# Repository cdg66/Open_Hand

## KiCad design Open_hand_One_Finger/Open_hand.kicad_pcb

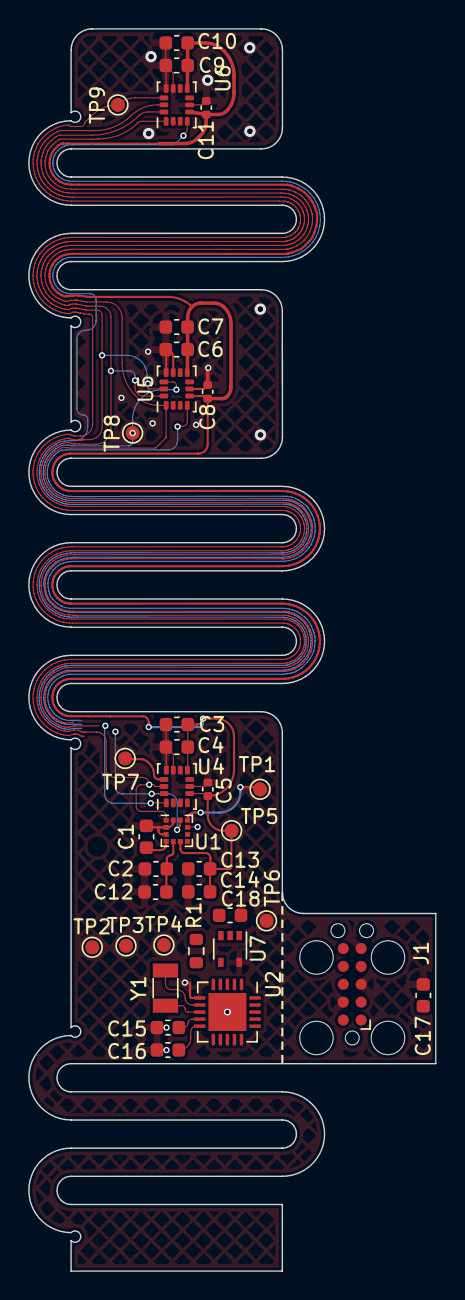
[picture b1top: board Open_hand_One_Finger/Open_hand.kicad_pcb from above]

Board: 2 copper layers, 28.9 x 88.2 mm, 37 parts (1 on the bottom side), 26 nets.

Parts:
C1, C2, C4, C7, C10, C14: 100n; C_0603_1608Metric
C3, C6, C9: 2u2; C_0603_1608Metric
C5, C8, C11: 10n; C_0402_1005Metric
C12, C13, C15, C16, C17, C18: 1u; C_0603_1608Metric
J1: Conn_ARM_JTAG_SWD_10; Tag-Connect_TC2050-IDC-FP_2x05_P1.27mm_Vertical
J2: DF37C-24DP-0.4V(51)
R1: R_US; R_0603_1608Metric
TP1, TP2, TP3, TP4, TP5, TP6, TP7, TP8, TP9: TestPoint; TestPoint_Pad_D1.0mm
U1: LIS3MDL; LGA-12_2x2mm_P0.5mm
U2: MAX32660GTP; TQFN-20-1EP_4x4mm_P0.5mm_EP2.7x2.7mm
U4, U5, U6: ICM-40608; LGA-14_3x2.5mm_P0.5mm_LayoutBorder3x4y
U7: SN74AHC1G02DCKR; SOT-353_SC-70-5
Y1: 32.768kHz,6pF; Crystal_SMD_3215-2Pin_3.2x1.5mm

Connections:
+3.3V: C2.1, C3.1, C4.1, C5.1, C6.1, C7.1, C8.1, C9.1, C10.1, C11.1, C12.1, C13.1, C14.1, C15.1, C17.1, C18.1, J1.1 (VTref), J2.6, J2.8, R1.1, TP5.1, U1.5 (Vdd), U1.6 (Vdd_IO), U2.9 (VDD), U4.5 (VDDIO), U4.8 (VDD), U5.5 (VDDIO), U5.8 (VDD), U6.5 (VDDIO), U6.8 (VDD), U7.3 (GND)
/CLK: J2.17, TP2.1, U1.1 (SCL/SPC), U2.16 (P0.6), U4.13 (AP_SCLK/AP_SCL), U5.13 (AP_SCLK/AP_SCL), U6.13 (AP_SCLK/AP_SCL)
/CS0: J2.15, TP7.1, U2.15 (P0.7), U4.12 (AP_CS)
/CS1: J2.13, TP8.1, U2.14 (P0.10), U5.12 (AP_CS)
/CS2: J2.11, TP9.1, U2.13 (P0.11), U6.12 (AP_CS)
/CS_MAG: J2.9, TP1.1, U1.10 (~CS), U2.4 (P0.12)
/DIN: J2.19, TP3.1, U1.11 (SDA/SDI/SDO), U2.17 (P0.5), U4.14 (AP_SDI/AP_SDIO/AP_SDA), U5.14 (AP_SDI/AP_SDIO/AP_SDA), U6.14 (AP_SDI/AP_SDIO/AP_SDA)
/DOUT: J2.21, TP4.1, U1.9 (SDO/SA1), U2.18 (P0.4), U4.1 (AP_SDO/AP_AD0), U5.1 (AP_SDO/AP_AD0), U6.1 (AP_SDO/AP_AD0)
/DREADY: J2.4, U1.8 (DRDY), U7.2
/INT0: J2.5, U4.4 (INT1/INT)
/INT1: J2.3, U5.4 (INT1/INT)
/INT2: J2.2, U6.4 (INT1/INT), U7.1
/INT_MAG: J2.1, U1.7 (INT)
/RST: J1.10 (~RESET), R1.2, U2.5 (~RSTN)
/SWCLK: J1.4 (SWDCLK/TCK), J2.14, U2.11 (P0.9)
/SWIO: J1.2 (SWDIO/TMS), J2.12, U2.12 (P0.8)
/UFP_CLK: J2.20, U2.20 (P0.2)
/UFP_CS: J2.22, U2.19 (P0.3)
/UFP_MISO: J2.16, U2.2 (P0.0)
/UFP_MOSI: J2.18, U2.1 (P0.1)
GND: C1.2, C2.2, C3.2, C4.2, C5.2, C6.2, C7.2, C8.2, C9.2, C10.2, C11.2, C12.2, C13.2, C14.2, C15.2, C16.2, C17.2, C18.2, J1.3 (GND), J1.5 (GND), J1.9 (GNDDetect), J2.7, J2.10, J2.23, J2.24, TP6.1, U1.2 (GND), U1.3 (GND), U1.12 (GND), U2.6 (V_{SS}), U2.21 (V_{SS}), U4.6 (GND), U4.10 (RESV), U4.11 (RESV), U5.6 (GND), U5.10 (RESV), U5.11 (RESV), U6.6 (GND), U6.10 (RESV), U6.11 (RESV), U7.5 (VCC)
unnamed: C1.1, U1.4 (C1)
unnamed: U2.8 (32KIN), Y1.1
unnamed: U2.7 (32KOUT), Y1.2
unnamed: U2.3 (P0.13), U7.4
unnamed: C16.1, U2.10 (VCORE)

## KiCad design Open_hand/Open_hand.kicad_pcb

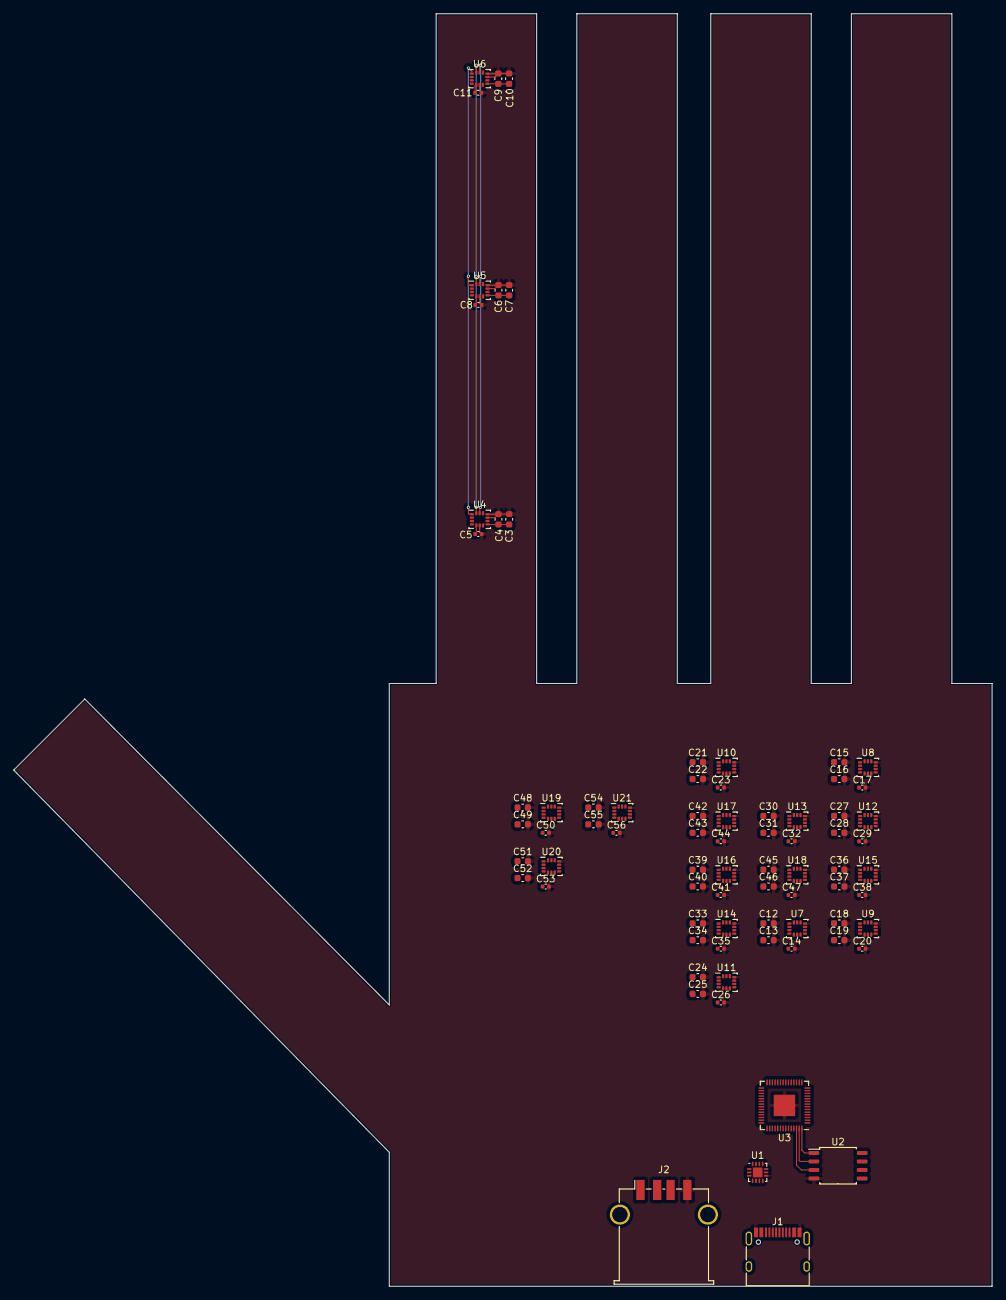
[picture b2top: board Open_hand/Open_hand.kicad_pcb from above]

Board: 2 copper layers, 146.1 x 190.0 mm, 77 parts (0 on the bottom side), 20 nets.

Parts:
C3, C6, C9, C12, C15, C18, C21, C24, C27, C30, C33, C36, C39, C42, C45, C48, C51, C54: 2u2; C_0603_1608Metric
C4, C7, C10, C13, C16, C19, C22, C25, C28, C31, C34, C37, C40, C43, C46, C49, C52, C55: 100n; C_0603_1608Metric
C5, C8, C11, C14, C17, C20, C23, C26, C29, C32, C35, C38, C41, C44, C47, C50, C53, C56: 10n; C_0402_1005Metric
J1: USB_C_Receptacle_USB2.0; USB_C_Receptacle_HRO_TYPE-C-31-M-12
J2: USB_A; USB_A_TE_292303-7_Horizontal
U1: FUSB302B10MPX; WQFN-14-1EP_2.5x2.5mm_P0.5mm_EP1.45x1.45mm
U2: W25Q16JVSS; SOIC-8_5.23x5.23mm_P1.27mm
U3: RP2040; QFN-56-1EP_7x7mm_P0.4mm_EP3.2x3.2mm
U4, U5, U6, U7, U8, U9, U10, U11, U12, U13, U14, U15, U16, U17, U18, U19, U20, U21: ICM-40608; LGA-14_3x2.5mm_P0.5mm_LayoutBorder3x4y

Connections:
+3.3V: C3.1, C4.1, C5.1, C6.1, C7.1, C8.1, C9.1, C10.1, C11.1, C12.1, C13.1, C14.1, C15.1, C16.1, C17.1, C18.1, C19.1, C20.1, C21.1, C22.1, C23.1, C24.1, C25.1, C26.1, C27.1, C28.1, C29.1, C30.1, C31.1, C32.1, C33.1, C34.1, C35.1, C36.1, C37.1, C38.1, C39.1, C40.1, C41.1, C42.1, C43.1, C44.1, C45.1, C46.1, C47.1, C48.1, C49.1, C50.1, C51.1, C52.1, C53.1, C54.1, C55.1, C56.1, U1.3 (VDD), U1.4 (VDD), U4.5 (VDDIO), U4.8 (VDD), U5.5 (VDDIO), U5.8 (VDD), U6.5 (VDDIO), U6.8 (VDD), U7.5 (VDDIO), U7.8 (VDD), U8.5 (VDDIO), U8.8 (VDD), U9.5 (VDDIO), U9.8 (VDD), U10.5 (VDDIO), U10.8 (VDD), U11.5 (VDDIO), U11.8 (VDD), U12.5 (VDDIO), U12.8 (VDD), U13.5 (VDDIO), U13.8 (VDD), U14.5 (VDDIO), U14.8 (VDD), U15.5 (VDDIO), U15.8 (VDD), U16.5 (VDDIO), U16.8 (VDD), U17.5 (VDDIO), U17.8 (VDD), U18.5 (VDDIO), U18.8 (VDD), U19.5 (VDDIO), U19.8 (VDD), U20.5 (VDDIO), U20.8 (VDD), U21.5 (VDDIO), U21.8 (VDD)
/CLK: U4.13 (AP_SCLK/AP_SCL), U5.13 (AP_SCLK/AP_SCL), U6.13 (AP_SCLK/AP_SCL), U7.13 (AP_SCLK/AP_SCL), U8.13 (AP_SCLK/AP_SCL), U9.13 (AP_SCLK/AP_SCL), U10.13 (AP_SCLK/AP_SCL), U11.13 (AP_SCLK/AP_SCL), U12.13 (AP_SCLK/AP_SCL), U13.13 (AP_SCLK/AP_SCL), U14.13 (AP_SCLK/AP_SCL), U15.13 (AP_SCLK/AP_SCL), U16.13 (AP_SCLK/AP_SCL), U17.13 (AP_SCLK/AP_SCL), U18.13 (AP_SCLK/AP_SCL), U19.13 (AP_SCLK/AP_SCL), U20.13 (AP_SCLK/AP_SCL), U21.13 (AP_SCLK/AP_SCL)
/CPU/D_M: J1.A7 (D-), J1.B7 (D-), U3.46 (USB_DM)
/CPU/D_P: J1.A6 (D+), J1.B6 (D+), U3.47 (USB_DP)
/DIN: U4.14 (AP_SDI/AP_SDIO/AP_SDA), U5.14 (AP_SDI/AP_SDIO/AP_SDA), U6.14 (AP_SDI/AP_SDIO/AP_SDA), U7.14 (AP_SDI/AP_SDIO/AP_SDA), U8.14 (AP_SDI/AP_SDIO/AP_SDA), U9.14 (AP_SDI/AP_SDIO/AP_SDA), U10.14 (AP_SDI/AP_SDIO/AP_SDA), U11.14 (AP_SDI/AP_SDIO/AP_SDA), U12.14 (AP_SDI/AP_SDIO/AP_SDA), U13.14 (AP_SDI/AP_SDIO/AP_SDA), U14.14 (AP_SDI/AP_SDIO/AP_SDA), U15.14 (AP_SDI/AP_SDIO/AP_SDA), U16.14 (AP_SDI/AP_SDIO/AP_SDA), U17.14 (AP_SDI/AP_SDIO/AP_SDA), U18.14 (AP_SDI/AP_SDIO/AP_SDA), U19.14 (AP_SDI/AP_SDIO/AP_SDA), U20.14 (AP_SDI/AP_SDIO/AP_SDA), U21.14 (AP_SDI/AP_SDIO/AP_SDA)
/DOUT: U4.1 (AP_SDO/AP_AD0), U5.1 (AP_SDO/AP_AD0), U6.1 (AP_SDO/AP_AD0), U7.1 (AP_SDO/AP_AD0), U8.1 (AP_SDO/AP_AD0), U9.1 (AP_SDO/AP_AD0), U10.1 (AP_SDO/AP_AD0), U11.1 (AP_SDO/AP_AD0), U12.1 (AP_SDO/AP_AD0), U13.1 (AP_SDO/AP_AD0), U14.1 (AP_SDO/AP_AD0), U15.1 (AP_SDO/AP_AD0), U16.1 (AP_SDO/AP_AD0), U17.1 (AP_SDO/AP_AD0), U18.1 (AP_SDO/AP_AD0), U19.1 (AP_SDO/AP_AD0), U20.1 (AP_SDO/AP_AD0), U21.1 (AP_SDO/AP_AD0)
GND: C3.2, C4.2, C5.2, C6.2, C7.2, C8.2, C9.2, C10.2, C11.2, C12.2, C13.2, C14.2, C15.2, C16.2, C17.2, C18.2, C19.2, C20.2, C21.2, C22.2, C23.2, C24.2, C25.2, C26.2, C27.2, C28.2, C29.2, C30.2, C31.2, C32.2, C33.2, C34.2, C35.2, C36.2, C37.2, C38.2, C39.2, C40.2, C41.2, C42.2, C43.2, C44.2, C45.2, C46.2, C47.2, C48.2, C49.2, C50.2, C51.2, C52.2, C53.2, C54.2, C55.2, C56.2, J1.A1 (GND), J1.A12 (GND), J1.B1 (GND), J1.B12 (GND), J2.4 (GND), U1.8 (GND), U1.9 (GND), U1.15 (GND), U2.4 (GND), U3.57 (GND), U4.6 (GND), U4.10 (RESV), U4.11 (RESV), U5.6 (GND), U5.10 (RESV), U5.11 (RESV), U6.6 (GND), U6.10 (RESV), U6.11 (RESV), U7.6 (GND), U7.10 (RESV), U7.11 (RESV), U8.6 (GND), U8.10 (RESV), U8.11 (RESV), U9.6 (GND), U9.10 (RESV), U9.11 (RESV), U10.6 (GND), U10.10 (RESV), U10.11 (RESV), U11.6 (GND), U11.10 (RESV), U11.11 (RESV), U12.6 (GND), U12.10 (RESV), U12.11 (RESV), U13.6 (GND), U13.10 (RESV), U13.11 (RESV), U14.6 (GND), U14.10 (RESV), U14.11 (RESV), U15.6 (GND), U15.10 (RESV), U15.11 (RESV), U16.6 (GND), U16.10 (RESV), U16.11 (RESV), U17.6 (GND), U17.10 (RESV), U17.11 (RESV), U18.6 (GND), U18.10 (RESV), U18.11 (RESV), U19.6 (GND), U19.10 (RESV), U19.11 (RESV), U20.6 (GND), U20.10 (RESV), U20.11 (RESV), U21.6 (GND), U21.10 (RESV), U21.11 (RESV)
unnamed: J1.A5 (CC1), U1.10 (CC1), U1.11 (CC1)
unnamed: J1.B5 (CC2), U1.1 (CC2), U1.14 (CC2)
unnamed: J2.3 (D+), U3.27 (GPIO16)
unnamed: J2.2 (D-), U3.28 (GPIO17)
unnamed: U2.6 (CLK), U3.52 (QSPI_SCLK)
unnamed: U2.5 (DI(IO0)), U3.53 (QSPI_SD0)
unnamed: U2.2 (DO(IO1)), U3.55 (QSPI_SD1)
unnamed: U2.3 (IO2), U3.54 (QSPI_SD2)
unnamed: U2.7 (IO3), U3.51 (QSPI_SD3)
unnamed: U2.1 (~CS), U3.56 (QSPI_SS)
unnamed: U3.23 (DVDD), U3.50 (DVDD)
unnamed: U3.1 (IOVDD), U3.10 (IOVDD), U3.22 (IOVDD), U3.33 (IOVDD), U3.42 (IOVDD), U3.49 (IOVDD)
VBUS: J1.A4 (VBUS), J1.A9 (VBUS), J1.B4 (VBUS), J1.B9 (VBUS), U1.2 (VBUS)

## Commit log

2023-04-16 first draft
2023-04-16 updat on the schematic side
2023-04-17 ONE FIGNER FLEX PCB
2023-04-17 add swd conector
2023-04-17 making the pcb look less like a dick
2023-04-18 adding coverlay slit so emi shield is connected to gnd more routing
2023-04-19 new copper pour rules
2023-04-19 ajout des infos dans la cartouche
